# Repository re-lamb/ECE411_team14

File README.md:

# ECE411_team14
practicum for ece411 fall '23

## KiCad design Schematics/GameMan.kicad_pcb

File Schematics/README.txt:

All schematics will be stored here. 
This includes circuit schematics as well as PCB layouts.
All entries will include a version number, as well as a date of submission/completion.

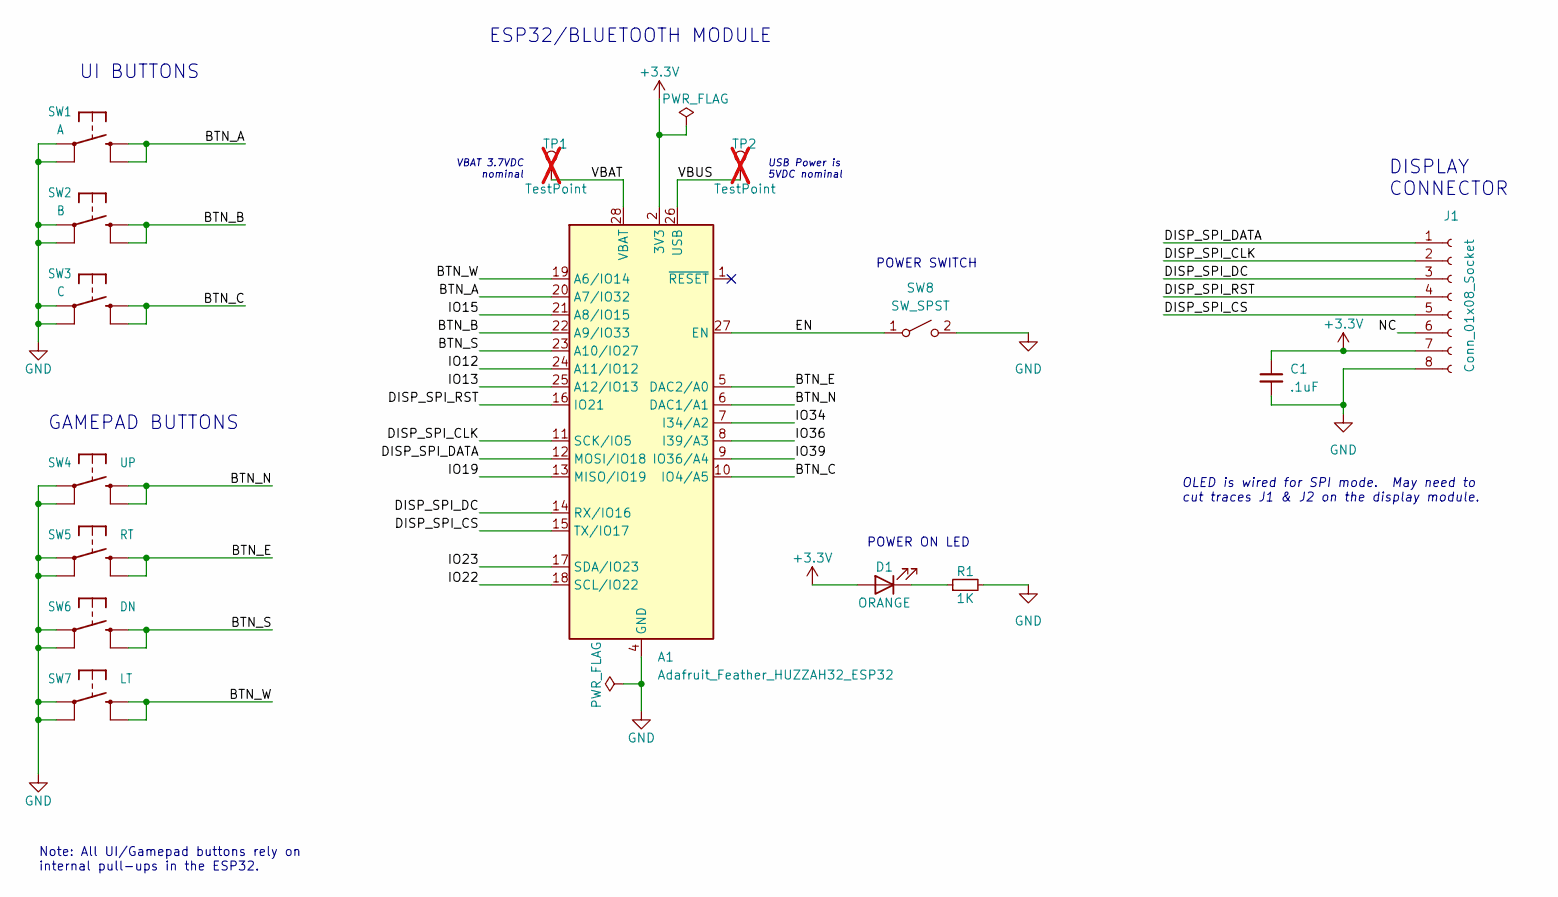
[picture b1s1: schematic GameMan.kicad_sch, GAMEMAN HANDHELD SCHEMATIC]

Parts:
A1: Adafruit_Feather_HUZZAH32_ESP32; Adafruit_Feather
C1: .1uF; 0805-NO
D1: ORANGE; CHIPLED_0805_NOOUTLINE
J1: Conn_01x08_Socket; Adafruit_SSD1327
R1: 1K; 0805-NO
SW1: A; SW_SPST_PTS645
SW2: B; SW_SPST_PTS645
SW3: C; SW_SPST_PTS645
SW4: UP; SW_SPST_PTS645
SW5: RT; SW_SPST_PTS645
SW6: DN; SW_SPST_PTS645
SW7: LT; SW_SPST_PTS645
SW8: SW_SPST; SW_SPDT_PCM12
TP1, TP2: TestPoint; PinHeader_1x01_P2.54mm_Vertical; not fitted

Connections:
+3.3V: A1.2 (3V3), C1.1, D1.2 (A), J1.7
/BTN_A: A1.20 (A7/IO32), SW1.2 (S)
/BTN_B: A1.22 (A9/IO33), SW2.2 (S)
/BTN_C: A1.10 (IO4/A5), SW3.2 (S)
/BTN_E: A1.5 (DAC2/A0), SW5.2 (S)
/BTN_N: A1.6 (DAC1/A1), SW4.2 (S)
/BTN_S: A1.23 (A10/IO27), SW6.2 (S)
/BTN_W: A1.19 (A6/IO14), SW7.2 (S)
/DISP_SPI_CLK: A1.11 (SCK/IO5), J1.2
/DISP_SPI_CS: A1.15 (TX/IO17), J1.5
/DISP_SPI_DATA: A1.12 (MOSI/IO18), J1.1
/DISP_SPI_DC: A1.14 (RX/IO16), J1.3
/DISP_SPI_RST: A1.16 (IO21), J1.4
/EN: A1.27 (EN), SW8.1 (A)
/IO12: A1.24 (A11/IO12)
/IO13: A1.25 (A12/IO13)
/IO15: A1.21 (A8/IO15)
/IO19: A1.13 (MISO/IO19)
/IO22: A1.18 (SCL/IO22)
/IO23: A1.17 (SDA/IO23)
/IO34: A1.7 (I34/A2)
/IO36: A1.8 (I39/A3)
/IO39: A1.9 (IO36/A4)
/NC: J1.6
/VBAT: A1.28 (VBAT), TP1.1
/VBUS: A1.26 (USB), TP2.1
GND: A1.4 (GND), C1.2, J1.8, R1.2, SW1.1, SW2.1, SW3.1, SW4.1, SW5.1, SW6.1, SW7.1, SW8.2 (B)
unnamed: D1.1 (K), R1.1

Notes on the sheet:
USB Power is 5VDC nominal
POWER SWITCH
UI BUTTONS
POWER ON LED
Note: All UI/Gamepad buttons rely on internal pull-ups in the ESP32.
ESP32/BLUETOOTH MODULE
GAMEPAD BUTTONS
DISPLAY CONNECTOR
OLED is wired for SPI mode. May need to cut traces J1 & J2 on the display module.
VBAT 3.7VDC nominal

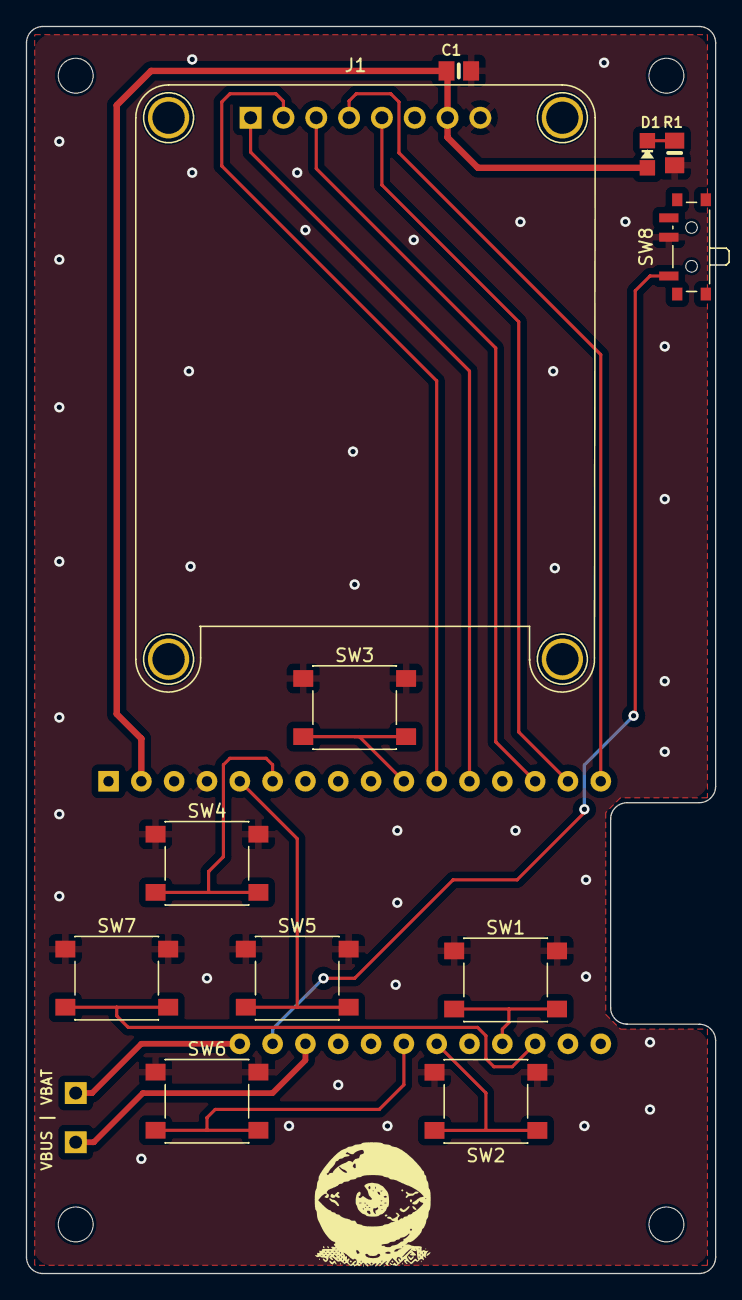
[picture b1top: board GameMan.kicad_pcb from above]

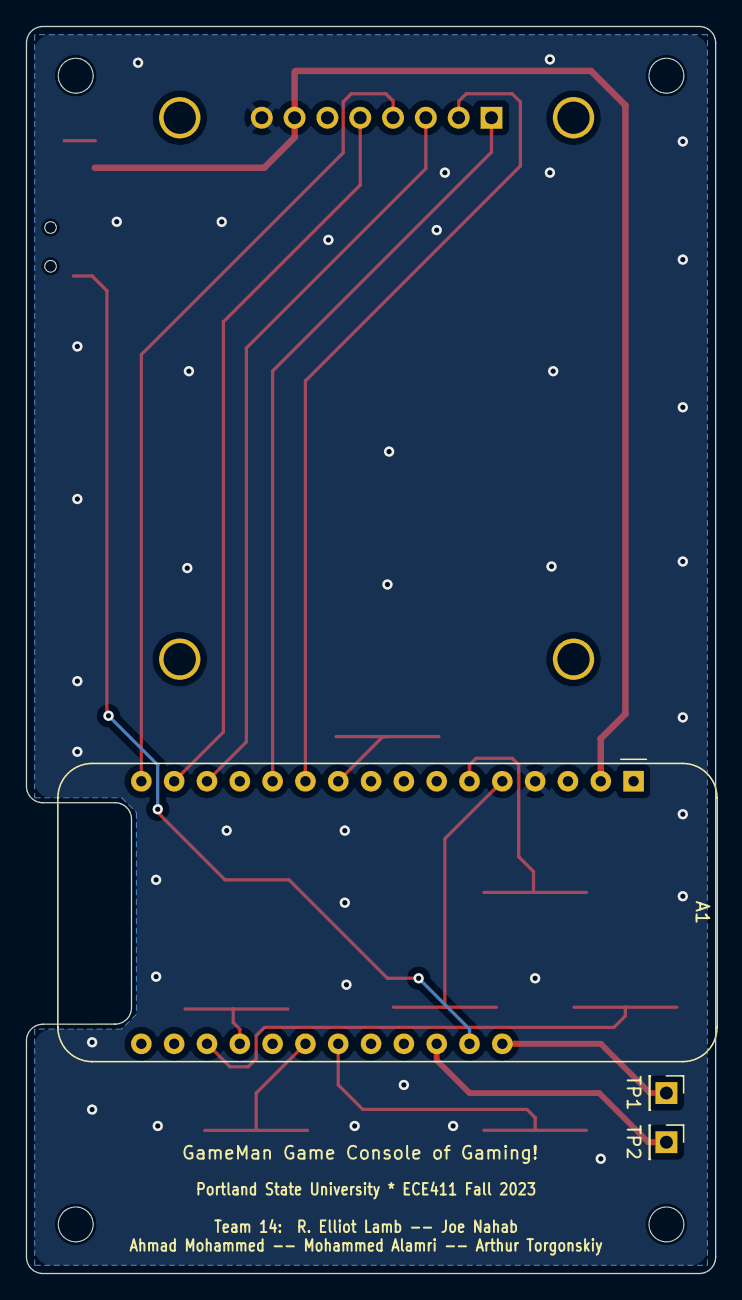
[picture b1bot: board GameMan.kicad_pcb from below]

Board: 2 copper layers, 53.3 x 96.5 mm, 15 parts (3 on the bottom side), 18 nets.

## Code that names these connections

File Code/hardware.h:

/*
 *  hardware.h - Buttons and pin assignments
 *
 *  Abstract:
 *      Defines the mapping of IO pins to the hardware as laid down
 *      on the GameMan PCB rev B1.
 *
 *  Team 14 Project
 *  Portland State University
 *  ECE411 Fall 2023
 */

#ifndef _GM_HARD_H_
#define _GM_HARD_H_

// Should match the schematic and PCB layout!
#define HW_VERSION  "B1"

// Pins used for software SPI (display connection)
#define OLED_CLK 5
#define OLED_MOSI 18

// Used for software or hardware SPI
#define OLED_CS 17
#define OLED_DC 16

// Used for I2C or SPI
#define OLED_RESET 21

// Define the GPIO pins for the direction pad, a/b/c buttons
#define IO_BTN_N  25    // north == up    -> pin labeled A1 on the Huzzah32
#define IO_BTN_E  26    // east == right  -> pin A0
#define IO_BTN_S  27    // south == down  -> pin IO27
#define IO_BTN_W  14    // west == left   -> pin IO14

#define IO_BTN_A  32    // -> pin IO32 on the Huzzah32
#define IO_BTN_B  33    // -> pin IO33
#define IO_BTN_C   4    // -> pin A5

// The ESP32-WROOM-32E has voltage sensing built in!
#define VBAT_SENSE  35

#endif

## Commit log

2023-10-12 Create LICENSE
    MIT license seems reasonable
2023-10-26 Schematic v1
2023-10-26 Schematic v1 - 10/25/23
2023-10-26 Create README.txt
    created readme for schematics folder
2023-10-26 Delete Schematic v1 - The GameMan Game Console of Gaming.pdf
    moving to schematics folder
2023-10-26 Delete The GameMan Game Console of Gaming - Schematic v1.pdf
    wrong ver.
2023-10-26 Schematic v1.0 - 10/25/23
2023-11-02 Gantt Chart 11/2/23
2023-11-02 Add files via upload
    Prototype status update
2023-11-02 Layout chematics v1.0
2023-11-02 Add files via upload
    BLE connection test
2023-11-02 PCB Schematic v1.0
2023-11-14 BOM - 11/9/23
2023-11-14 PCB Layout & Schematic v1.0e
2023-11-16 Delete Schematics directory
    Replacement on the way
2023-11-16 Add files via upload
    Version 2 schematic and PCB
2023-11-20 Add files via upload
    task framework for doing initialization/IO/menus
2023-12-05 adding networking stack
2023-12-08 Big update, mostly to TTT.
2023-12-08 version 0.85 snapshot. memory leaks abound.
2023-12-08 0.89 snapshot
